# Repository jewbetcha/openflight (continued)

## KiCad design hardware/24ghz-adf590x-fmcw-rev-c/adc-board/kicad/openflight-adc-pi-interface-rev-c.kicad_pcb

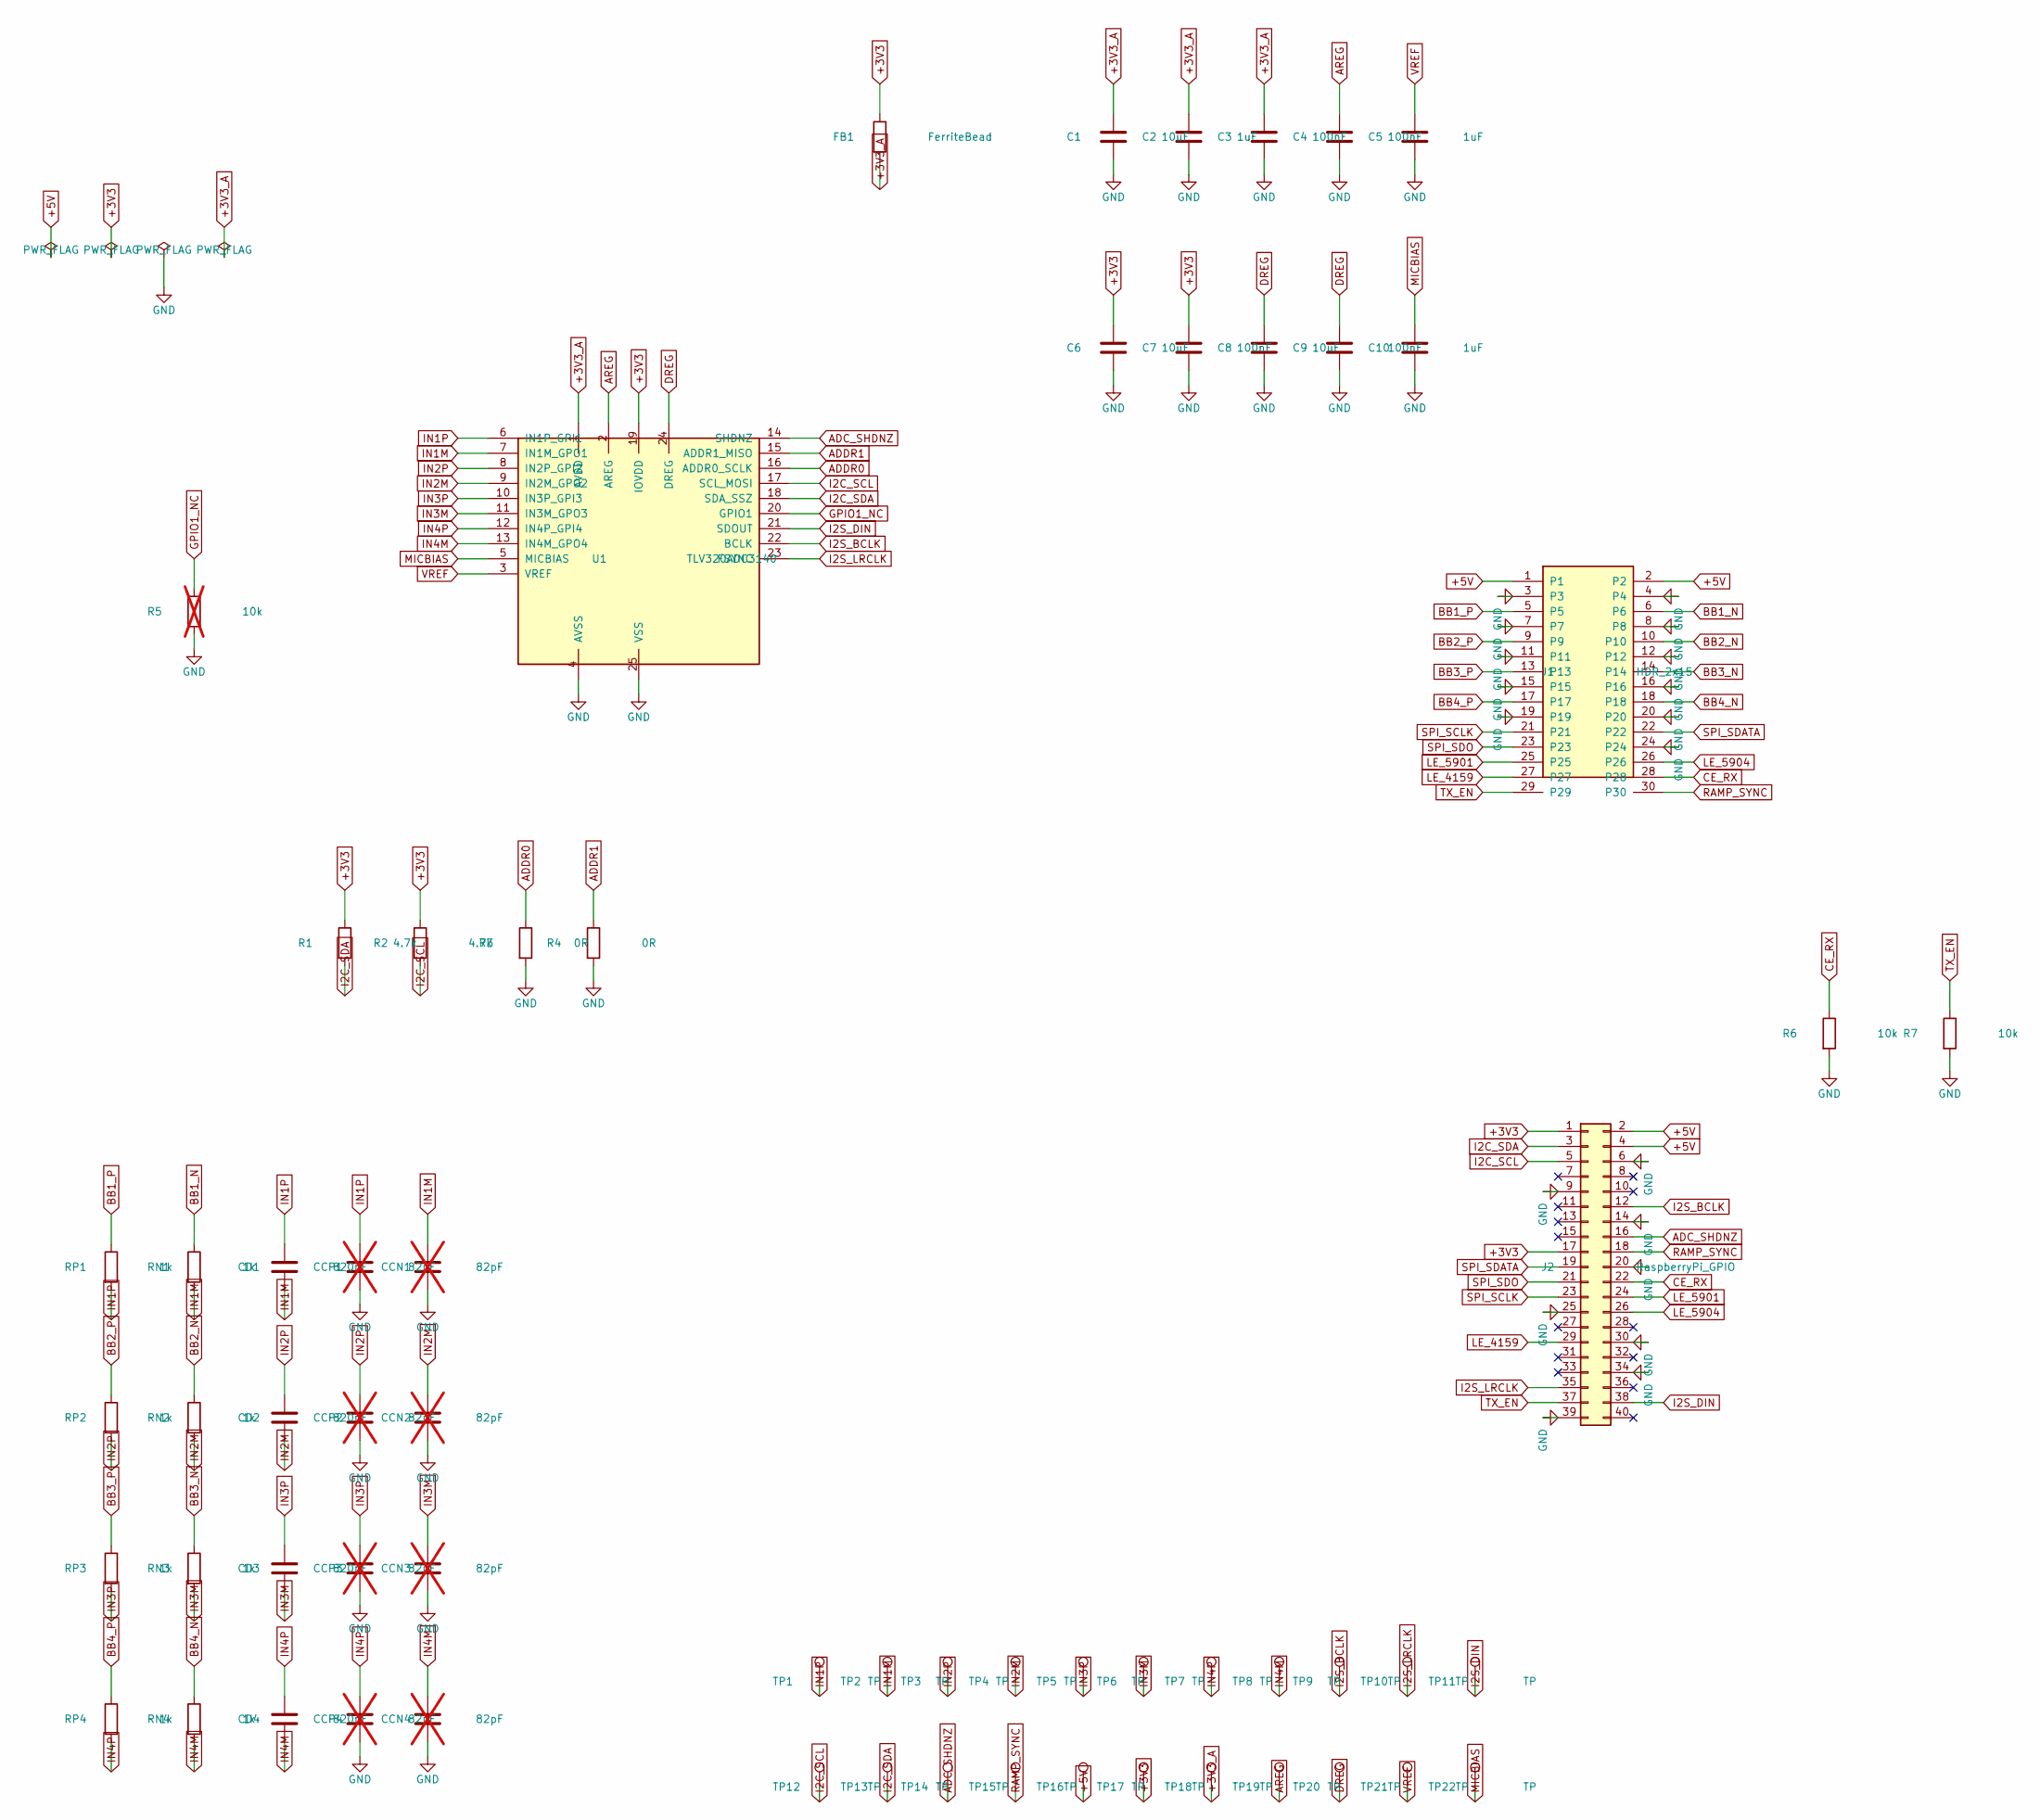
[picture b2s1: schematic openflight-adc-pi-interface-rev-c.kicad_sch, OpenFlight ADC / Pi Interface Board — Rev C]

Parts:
C1, C6, C8: 10uF; C_0402_1005Metric
C2, C5, C10: 1uF; C_0402_1005Metric
C3, C4, C7, C9: 100nF; C_0402_1005Metric
CCN1, CCN2, CCN3, CCN4: 82pF; C_0402_1005Metric; not fitted
CCP1, CCP2, CCP3, CCP4: 82pF; C_0402_1005Metric; not fitted
CD1, CD2, CD3, CD4: 820pF; C_0402_1005Metric
FB1: FerriteBead; R_0402_1005Metric
J1: HDR_2x15; HDR_2x15_1.27MM_SMD; MPN FTSH-115-01-L-DV-K
J2: RaspberryPi_GPIO; PinSocket_2x20_P2.54mm_Vertical; MPN ESQ-120-58-S-D
R1, R2: 4.7k; R_0402_1005Metric
R3, R4: 0R; R_0402_1005Metric
R5: 10k; R_0402_1005Metric; not fitted
R6, R7: 10k; R_0402_1005Metric; MPN RC0402FR-0710KL
RN1, RN2, RN3, RN4: 1k; R_0402_1005Metric
RP1, RP2, RP3, RP4: 1k; R_0402_1005Metric
TP1, TP2, TP3, TP4, TP5, TP6, TP7, TP8, TP9, TP10, TP11, TP12, TP13, TP14, TP15, TP16, TP17, TP18, TP19, TP20, TP21, TP22: TP; TestPoint_Pad_D1.5mm
U1: TLV320ADC3140; TLV320ADC3140_WQFN24; MPN TLV320ADC3140IRTWT

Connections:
+3V3: C6.1, C7.1, FB1.1, J2.1, J2.17, R1.1, R2.1, TP17.1, U1.19 (IOVDD)
+3V3_A: C1.1, C2.1, C3.1, FB1.2, TP18.1, U1.1 (AVDD)
+5V: J1.1, J1.2, J2.2, J2.4, TP16.1
ADC_SHDNZ: J2.16, TP14.1, U1.14 (SHDNZ)
ADDR0: R3.1, U1.16 (ADDR0_SCLK)
ADDR1: R4.1, U1.15 (ADDR1_MISO)
AREG: C4.1, TP19.1, U1.2 (AREG)
BB1_N: J1.6, RN1.1
BB1_P: J1.5, RP1.1
BB2_N: J1.10, RN2.1
BB2_P: J1.9, RP2.1
BB3_N: J1.14, RN3.1
BB3_P: J1.13, RP3.1
BB4_N: J1.18, RN4.1
BB4_P: J1.17, RP4.1
CE_RX: J1.28, J2.22, R6.1
DREG: C8.1, C9.1, TP20.1, U1.24 (DREG)
GND: C1.2, C2.2, C3.2, C4.2, C5.2, C6.2, C7.2, C8.2, C9.2, C10.2, CCN1.2, CCN2.2, CCN3.2, CCN4.2, CCP1.2, CCP2.2, CCP3.2, CCP4.2, J1.3, J1.4, J1.7, J1.8, J1.11, J1.12, J1.15, J1.16, J1.19, J1.20, J1.24, J2.6, J2.9, J2.14, J2.20, J2.25, J2.30, J2.34, J2.39, R3.2, R4.2, R5.2, R6.2, R7.2, U1.4 (AVSS), U1.25 (VSS)
GPIO1_NC: R5.1, U1.20 (GPIO1)
I2C_SCL: J2.5, R2.2, TP12.1, U1.17 (SCL_MOSI)
I2C_SDA: J2.3, R1.2, TP13.1, U1.18 (SDA_SSZ)
I2S_BCLK: J2.12, TP9.1, U1.22 (BCLK)
I2S_DIN: J2.38, TP11.1, U1.21 (SDOUT)
I2S_LRCLK: J2.35, TP10.1, U1.23 (FSYNC)
IN1M: CCN1.1, CD1.2, RN1.2, TP2.1, U1.7 (IN1M_GPO1)
IN1P: CCP1.1, CD1.1, RP1.2, TP1.1, U1.6 (IN1P_GPI1)
IN2M: CCN2.1, CD2.2, RN2.2, TP4.1, U1.9 (IN2M_GPO2)
IN2P: CCP2.1, CD2.1, RP2.2, TP3.1, U1.8 (IN2P_GPI2)
IN3M: CCN3.1, CD3.2, RN3.2, TP6.1, U1.11 (IN3M_GPO3)
IN3P: CCP3.1, CD3.1, RP3.2, TP5.1, U1.10 (IN3P_GPI3)
IN4M: CCN4.1, CD4.2, RN4.2, TP8.1, U1.13 (IN4M_GPO4)
IN4P: CCP4.1, CD4.1, RP4.2, TP7.1, U1.12 (IN4P_GPI4)
LE_4159: J1.27, J2.29
LE_5901: J1.25, J2.24
LE_5904: J1.26, J2.26
MICBIAS: C10.1, TP22.1, U1.5 (MICBIAS)
RAMP_SYNC: J1.30, J2.18, TP15.1
SPI_SCLK: J1.21, J2.23
SPI_SDATA: J1.22, J2.19
SPI_SDO: J1.23, J2.21
TX_EN: J1.29, J2.37, R7.1
VREF: C5.1, TP21.1, U1.3 (VREF)

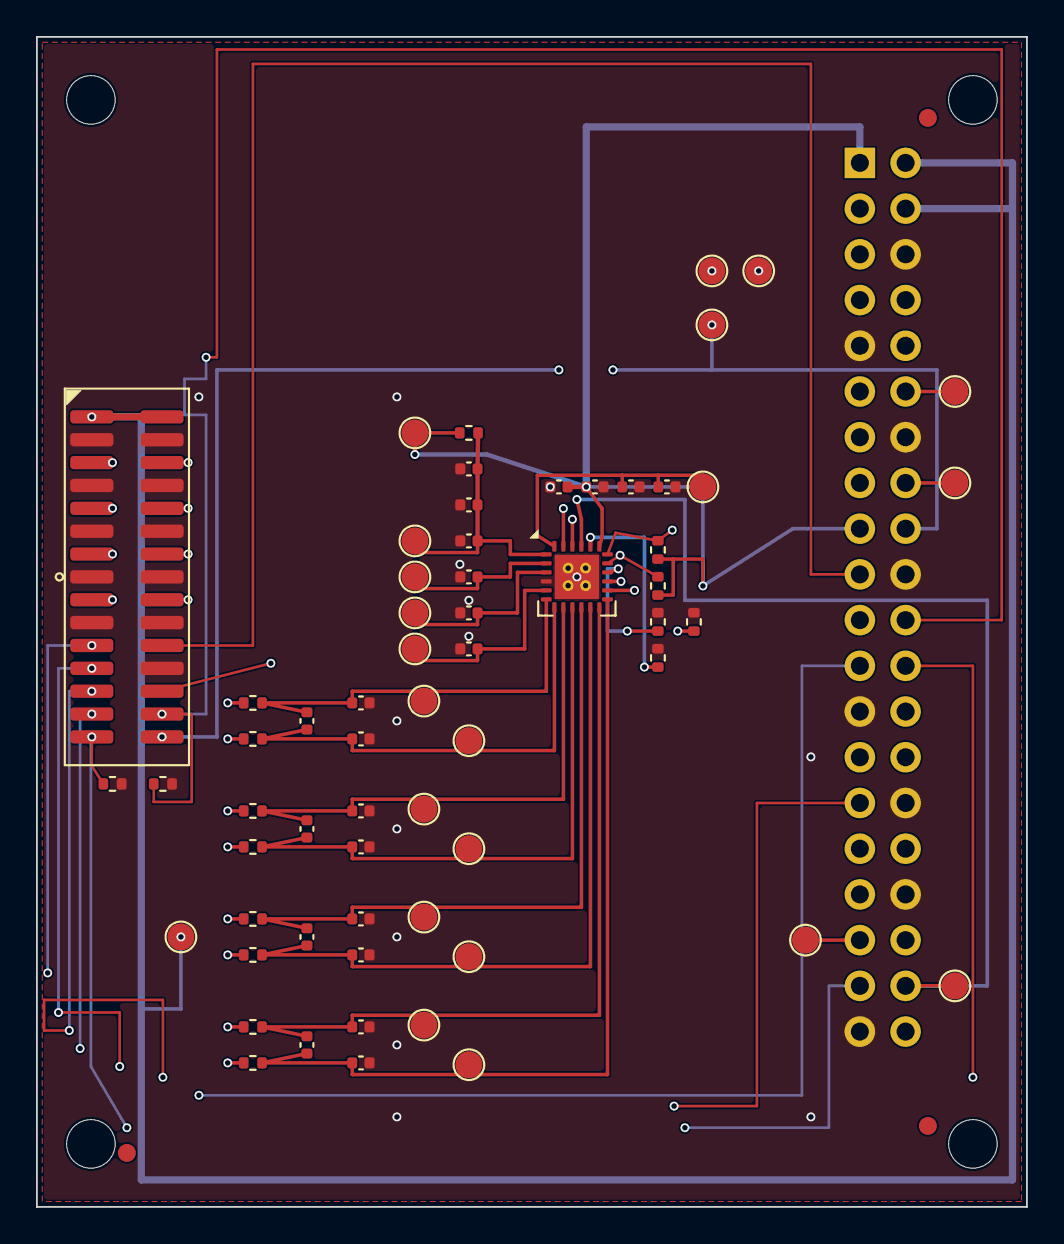
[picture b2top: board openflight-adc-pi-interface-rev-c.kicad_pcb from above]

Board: 4 copper layers, 55.0 x 65.0 mm, 70 parts (1 on the bottom side), 42 nets.

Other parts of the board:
FID1, FID2, FID3: Fiducial_1mm
H1, H2, H3, H4: MountingHole_2.7mm

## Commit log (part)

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2025-12-09 [cr] restructure for OPS243
2025-12-09 [cr] update API methods
2025-12-09 [cr] remove content dir
2025-12-11 [cr] add logo
2025-12-17 [cr] more tests
2025-12-17 [cr] add parts list
2025-12-17 [cr] camera debug
2025-12-18 [cr] debug circle detection
2025-12-18 [cr] pi docs
2025-12-19 [cr] debug and tune mode
2025-12-21 [cr] try ml detection
2025-12-23 [cr] new model
2025-12-23 [cr] working on performance for camera
2025-12-23 [cr] rearrange docs
2025-12-26 [cr] new color palatte, debug mode also captures camera information
2025-12-28 [cr] fix inbound/outbound bug
2025-12-28 [cr] lower default ball speed
2025-12-28 [cr] more debug
2025-12-28 [cr] finally filter inbound?
2025-12-29 [cr] enable direction reporting
2025-12-29 [cr] please, outbound only
2026-01-04 [cr] big refactor to cleanup, multi-object detection
2026-01-04 [cr] debug multi-object detect
2026-01-05 Add Serialize to shot types and minor code cleanup
    Derive Serialize for Direction, SpeedReading, and ClubType in shot.rs to enable serialization. Remove unused mut in launch_monitor.rs and ops243.rs.
2026-01-06 Rename README-RUST.md to README.md
2026-01-06 [cr] new official OPS docs, update API config to match specific golf docs
2026-01-07 move rust to central location
2026-01-07 1.6.26 python changes to rust
2026-01-07 Send all data to OGS - if not we crash the app
2026-01-07 [cr] fix lint job
2026-01-13 [cr] desktop icon for rolling buffer mode
2026-01-13 [cr] fix scripts to accept --mode arg
2026-01-13 [cr] logging to debug rolling buffer mode
2026-01-13 [cr] update tests
2026-01-15 [cr] adjust rolling buffer trigger threshold
2026-01-16 [cr] try to diagnose FFT
2026-01-17 [cr] raw iq capture script
2026-01-19 [cr] ignore pkl files
2026-01-19 [cr] init claude file, update capture script for streaming mode
2026-01-19 [cr] add analysis deps to setup
2026-01-20 [cr] remove old filters
2026-01-20 [cr] debug some readings
2026-01-20 [cr] damnit claude
2026-01-20 [cr] pass debug to startup script
2026-01-21 [cr] trying a new detection algo, seems slightly better
2026-01-21 [cr] more verbose logging
2026-01-23 [cr] install some claude skills
2026-01-26 [cr] lots of updates to radar settings
2026-01-28 [cr] bytetrack test script
2026-01-28 [cr] update pyproject
2026-01-28 [cr] dial in detect script
2026-01-28 [cr] small change to camera detect threshold
2026-01-28 [cr] more code cleanup, remove tests for py 3.9
2026-01-29 Add more clubs to the club picker
    I was playing around with the UI and noticed that the club selection was
    a little bit limited. While it's probably okay to use e.g. 5-wood when
    practicing with a hybrid, I thought it would be better to have the right
    club in the list. The list is of course not complete ("where's my
    1-iron?") but it should be enough for 99.5% of golfers.
    I picked enough clubs so that they would be divisible by four. The grid
2026-01-30 Add Storybook for the App component
    To make UI development even simpler, I'm adding Storybook to the
    project. This makes it easier to iterate on styling and keeps the
    application at a clean cut between data and UI. It also makes it easier
    to add visual regression testing tools like e.g. Happo (full disclosure:
    I work there).
2026-01-30 Test commit for maintainer
2026-01-30 [cr] codeowners
2026-01-30 Animate ClubPicker dropdown on close
    I noticed the opening of the dropdown is animated with a fade-in + some
    transform. But closing the dialog was abrupt. We can make this better by
    making use of a transition instead of an animation, and usage of
    @starting-style + allow-discrete to keep the element visible long enough
    for the transition animation to happen.
    Used this as a guide: https://frontendmasters.com/blog/animating-dialog/
2026-02-05 [cr] install python performance skills
2026-02-05 [cr] implement GIPO passthrough for ultra low-latency trigger
2026-02-05 [cr] add script for testing GIPO passthrough
2026-02-05 [cr] debug gpio passthrough
2026-02-05 [cr] debug rolling buffer mode
2026-02-05 [cr] diagnostic script
2026-02-05 [cr] test software trigger
2026-02-06 [cr] more logging
2026-02-09 [cr] testing sound trigger
2026-02-10 Prevent text selection when triggering Launch Daddy mode
    When you trigger Launch Daddy mode, the rapid clicking triggers text to
    be selected. We can use some css to prevent this unwanted side-effect.
2026-02-10 Fix triggering Launch Daddy in React strict mode
    When running the ui in dev mode, I noticed that the launch daddy trigger
    didn't work. The counter would increment but the mode never changed. I
    think this is related to how state is handled in strict mode, and how
    the isLaunchDaddyMode state was updated inside the state-setting
    callback for secretTapCount.
    To fix this I kept the a separate ref counter of the same value. I first
2026-02-12 [cr] new pass on FFT and tabs on debug view
2026-02-12 [cr] measure latency more accurately, capture more pre-trigger data
2026-02-12 [cr] change default pre-trigger
2026-02-12 [cr] update kiosk icon
2026-02-19 [cr] log everything, even skipped shots
2026-02-19 [cr] more testing
2026-02-26 [cr] resample spin samples before FFT
2026-02-28 [cr] testing different settings, make sure to rearm with pre-trigger buffer
2026-03-01 [cr] test scripts for launch angle and spin
2026-03-01 [cr] fix launch angle test
2026-03-01 [cr] tune hough params, add launch angle to logs in shot data
2026-04-03 feat: add optional second kld7 tracker
2026-04-03 fix: preserve per-axis launch angle provenance
2026-04-13 Bump @vitejs/plugin-react from 5.1.2 to 6.0.1 in /ui
    Bumps [@vitejs/plugin-react](https://github.com/vitejs/vite-plugin-react/tree/HEAD/packages/plugin-react) from 5.1.2 to 6.0.1.
    - [Release notes](https://github.com/vitejs/vite-plugin-react/releases)
    - [Changelog](https://github.com/vitejs/vite-plugin-react/blob/main/packages/plugin-react/CHANGELOG.md)
    - [Commits](https://github.com/vitejs/vite-plugin-react/commits/plugin-react@6.0.1/packages/plugin-react)
    ---
    updated-dependencies:
2026-04-13 Update python-socketio requirement from >=5.10.0 to >=5.16.1
    Updates the requirements on [python-socketio](https://github.com/miguelgrinberg/python-socketio) to permit the latest version.
    - [Release notes](https://github.com/miguelgrinberg/python-socketio/releases)
    - [Changelog](https://github.com/miguelgrinberg/python-socketio/blob/main/CHANGES.md)
    - [Commits](https://github.com/miguelgrinberg/python-socketio/compare/v5.10.0...v5.16.1)
    ---
    updated-dependencies:
2026-04-19 Bump react-dom from 19.2.1 to 19.2.5 in /ui
    Bumps [react-dom](https://github.com/facebook/react/tree/HEAD/packages/react-dom) from 19.2.1 to 19.2.5.
    - [Release notes](https://github.com/facebook/react/releases)
    - [Changelog](https://github.com/facebook/react/blob/main/CHANGELOG.md)
    - [Commits](https://github.com/facebook/react/commits/v19.2.5/packages/react-dom)
    ---
    updated-dependencies:
2026-04-25 Fix rolling buffer shot timing
2026-04-26 Bump vite from 7.2.7 to 8.0.10 in /ui
    Bumps [vite](https://github.com/vitejs/vite/tree/HEAD/packages/vite) from 7.2.7 to 8.0.10.
    - [Release notes](https://github.com/vitejs/vite/releases)
    - [Changelog](https://github.com/vitejs/vite/blob/main/packages/vite/CHANGELOG.md)
    - [Commits](https://github.com/vitejs/vite/commits/v8.0.10/packages/vite)
    ---
    updated-dependencies:
2026-04-26 build(deps-dev): bump eslint from 9.39.1 to 10.2.1 in /ui
    Bumps [eslint](https://github.com/eslint/eslint) from 9.39.1 to 10.2.1.
    - [Release notes](https://github.com/eslint/eslint/releases)
    - [Commits](https://github.com/eslint/eslint/compare/v9.39.1...v10.2.1)
    ---
    updated-dependencies:
    - dependency-name: eslint
2026-05-03 build(deps-dev): bump eslint from 9.39.1 to 10.3.0 in /ui
    Bumps [eslint](https://github.com/eslint/eslint) from 9.39.1 to 10.3.0.
    - [Release notes](https://github.com/eslint/eslint/releases)
    - [Commits](https://github.com/eslint/eslint/compare/v9.39.1...v10.3.0)
    ---
    updated-dependencies:
    - dependency-name: eslint
2026-05-03 build(deps-dev): bump eslint-plugin-react-refresh in /ui
    Bumps [eslint-plugin-react-refresh](https://github.com/ArnaudBarre/eslint-plugin-react-refresh) from 0.4.24 to 0.5.2.
    - [Release notes](https://github.com/ArnaudBarre/eslint-plugin-react-refresh/releases)
    - [Changelog](https://github.com/ArnaudBarre/eslint-plugin-react-refresh/blob/main/CHANGELOG.md)
    - [Commits](https://github.com/ArnaudBarre/eslint-plugin-react-refresh/compare/v0.4.24...v0.5.2)
    ---
    updated-dependencies:
2026-05-03 build(deps-dev): bump @eslint/js from 9.39.1 to 10.0.1 in /ui
    Bumps [@eslint/js](https://github.com/eslint/eslint/tree/HEAD/packages/js) from 9.39.1 to 10.0.1.
    - [Release notes](https://github.com/eslint/eslint/releases)
    - [Commits](https://github.com/eslint/eslint/commits/v10.0.1/packages/js)
    ---
    updated-dependencies:
    - dependency-name: "@eslint/js"
2026-06-17 DESIGN
    - add the glass design tokens and theme color system
    - add the responsive root scale ramp and color-blind theme remap
2026-06-17 BACKEND
    - add /api/history and /api/history/<id>/shots endpoints reading the session JSONL logs
2026-06-17 UI
    - redesign the shot display with gauges, metrics, and spin provenance
2026-06-17 UI
    - add unit preferences (imperial/metric) and refresh the core components
2026-06-17 UI
    - add interactive, scoreboard, and phone-remote view modes
    - add D-pad spatial navigation and the focus-ring system
    - add view-mode detection and the /scoreboard and /remote routes
2026-06-17 UI
    - show the real angle source on the club AoA and club path cards
2026-06-17 UI
    - wire the app shell, socket handlers, and the redesign build config
2026-06-17 UI
    - pin the club-select close X so the focus ring can't shift it to the top-left
    - gate the TV focus ring behind real remote/keyboard nav so a mouse never gets a stuck ring
    - drop the gold pre-highlight on the current club
    - mark the club-select buttons type=button
2026-06-17 BACKEND
    - validate the USGA Cd/Cl drag-and-lift ballistics model against reference carry
    - use a 1 ms RK4 integration step
    - add dataclass docstrings and use the max() builtin
2026-06-17 BACKEND
    - expose the trajectory geometry on the shot payload
    - record the simulated apex height on each shot
2026-06-17 BACKEND
    - wire the BLE server into startup behind the --ble flag
    - load the pairing secret and serve it via the localhost /api/pair-qr endpoint
2026-06-17 BACKEND
    - advertise an OpenFlight GATT service via BlueZ so the mobile app connects without Wi-Fi
    - notify shots and session events, and handle club/session/prefs commands
    - authenticate with a rotating nonce and constant-time HMAC-SHA256 over a pairing key
2026-06-17 DOCS
    - add the BLE wire-protocol reference for the GATT server
    - note the BLE GATT peripheral in the changelog
2026-06-17 SECURITY
    - restrict CORS to a LAN-origin allowlist (localhost and RFC 1918 ranges) instead of open *
    - generate separate admin and camera-stream tokens at startup
2026-06-17 SECURITY
    - require the admin token on every mutating endpoint and socket event
    - update the radar-config tests to send the admin token
2026-06-17 SECURITY
    - validate radar-config ranges before applying them
    - keep the Roboflow API key out of argv
2026-06-17 BUILD
    - auto-detect the view mode (interactive vs scoreboard) at kiosk startup
    - pass a low-power hint for constrained GPUs
2026-06-17 BACKEND
    - add the /scoreboard display and /remote web-remote server routes
    - relay D-pad keys from the phone remote to the display over the socket
2026-06-18 chore: remove generated docs - shot-visualization and tv-remote (docs-only PR to follow)
2026-06-18 chore: remove generated user-guide.html (docs-only PR to follow)
2026-06-18 chore: remove generated user-guide.md (docs-only PR to follow)
2026-06-18 feat(ui): add glass design token system and theme
    Introduces tokens.css with CSS custom properties for all colors, spacing,
    radii, and shadows. Adds a responsive root scale ramp so the layout reflows
    from 7-inch touchscreen to 55-inch TV without manual breakpoints.
    Includes color-blind-safe remaps for deuteranopia (red/green indicators).
    useThemeColors.ts exposes the resolved token values to JS when needed.
